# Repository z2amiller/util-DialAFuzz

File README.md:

# util-DialAFuzz

A plug-in NPN transistor with a dial for hFE. Fuzz circuits are picky about
transistor gain, and modern Si transistors are usually too hot. This board plugs
into a TO-92 socket in place of the transistor and lets you trim the effective
hFE of an ordinary transistor down from its native ~300 to wherever the circuit
sounds right, without hunting for a rare low-gain part.

## How it works

Q2 is the transistor the pedal sees, wired straight across the header. Q1 is
diode-connected in parallel with Q2's base-emitter junction, with the trimmer
in its emitter leg, so it steals a settable share of the base current (a
Widlar split). Effective hFE rises roughly linearly with the trimmer
resistance, and scales with the stage's bias current, so the same setting
reads higher in a 1 mA stage than in a 50 µA one. Trim it in circuit.

LEAK is an optional 2.2M collector-base resistor (leave it off unless wanted).
It injects a small base current that the transistor multiplies, which mimics
the collector leakage of a germanium part, useful when running silicon in a
circuit designed around leaky germanium.

Header order is E, B, C. That matches 2N3904 / 2N5088 style sockets directly;
for a BC-series (C, B, E) socket, plug it in reversed.

## Example: Fuzz Face

PedalPCB's [SiliSmile Fuzz](https://www.pedalpcb.com/product/pcb582/) is a
silicon NPN Fuzz Face with socketed transistors, a good host.

Drop it into the Q1 socket with a BC847 (hFE ~300) and the trimmer covers
roughly hFE 9 at minimum to 240 at maximum. The classic germanium Q1 range of
70 to 100 lands around 200K to 300K. Set it the same way you would bias any
Fuzz Face: adjust for Q2's collector near 4.5 V, or by ear. Nothing is at risk
at either end of the travel; at the bottom the stage just biases wrong.

A companion board, [util-BleedAFuzz](https://github.com/z2amiller/util-BleedAFuzz),
does the same job with a single transistor and a base-emitter bleed, which
suits collector-feedback fuzzes better.

## Gerbers

[GERBER-util-DialAFuzz.zip](GERBER-util-DialAFuzz.zip) is the JLCPCB-ready
gerber and drill set; no KiCad install needed to order the board. Two SOT-23
BC847s (or whatever ~matched transistors you have), one 0805 resistor (optional),
a 3-pin header and a through-hole 1M trimmer on the back.

## License

Licensed under the **CERN Open Hardware Licence Version 2 – Permissive**
(CERN-OHL-P v2). See [LICENSE](LICENSE) and [NOTICE](NOTICE).

You may make, modify, and sell boards from these files, with no obligation to
publish your changes.

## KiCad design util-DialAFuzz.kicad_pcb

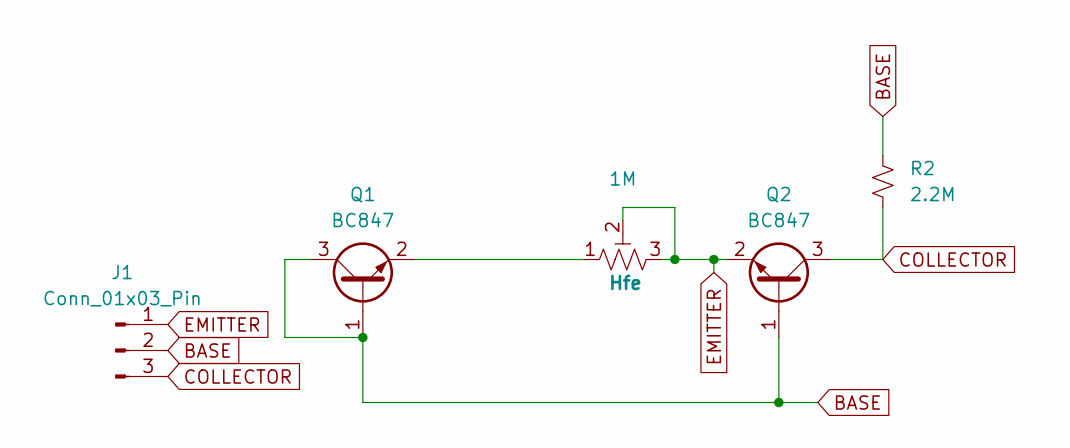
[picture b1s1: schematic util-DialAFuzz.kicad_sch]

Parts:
J1: Conn_01x03_Pin; PinHeader_1x03_P2.54mm_Vertical
Q1, Q2: BC847; SOT-23_Handsoldering
R2: 2.2M; R_0805_2012Metric_Pad1.20x1.40mm_HandSolder
RV1: 1M; Variable Trimmer

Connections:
BASE: J1.2, Q1.1 (B), Q1.3 (C), Q2.1 (B), R2.2
COLLECTOR: J1.3, Q2.3 (C), R2.1
EMITTER: J1.1, Q2.2 (E), RV1.2, RV1.3
unnamed: Q1.2 (E), RV1.1

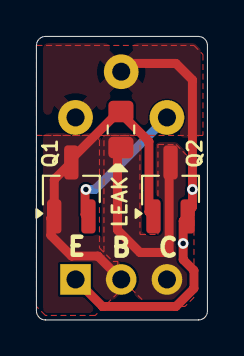
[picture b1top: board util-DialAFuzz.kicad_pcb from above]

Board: 2 copper layers, 9.5 x 15.8 mm, 5 parts (1 on the bottom side), 4 nets.
